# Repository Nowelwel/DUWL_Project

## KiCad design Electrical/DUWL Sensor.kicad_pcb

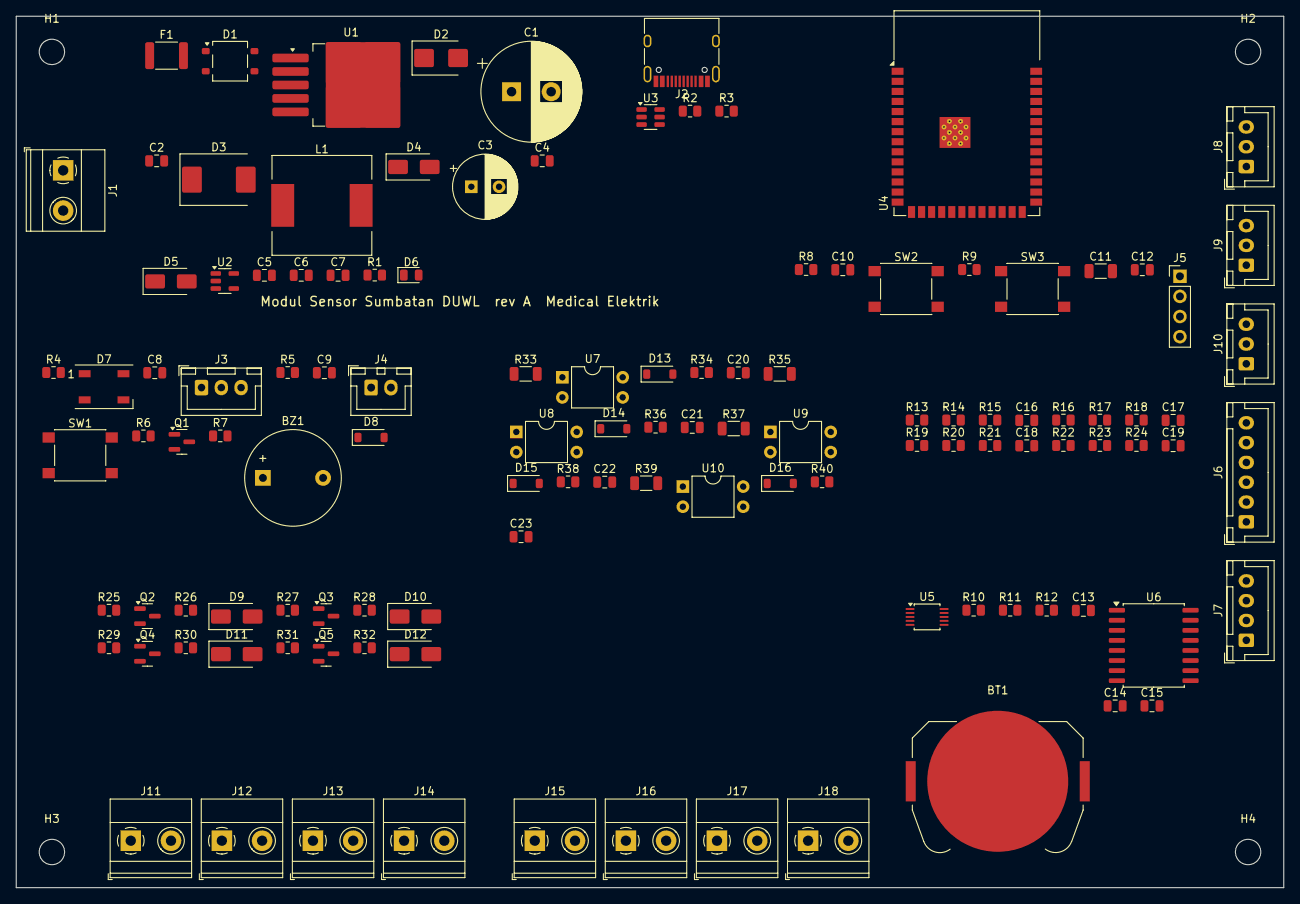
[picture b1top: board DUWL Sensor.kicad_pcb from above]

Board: 2 copper layers, 160.0 x 110.0 mm, 123 parts (0 on the bottom side), 69 nets, no tracks yet.

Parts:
BT1: CR2032; BatteryHolder_Keystone_3034_1x20mm
BZ1: Buzzer aktif 5V; Buzzer_12x9.5RM7.6
C1: 470u 63V; CP_Radial_D12.5mm_P5.00mm
C2: 100n 100V; C_0805_2012Metric
C3: 330u 16V; CP_Radial_D8.0mm_P3.50mm
C4, C7, C8, C9, C12, C13, C14, C15, C16, C17, C18, C19: 100nF; C_0805_2012Metric
C5, C6: 10uF; C_0805_2012Metric
C10, C20, C21, C22, C23: 1uF; C_0805_2012Metric
C11: 22uF; C_1206_3216Metric
D1: MB6S; TO-269AA
D2: SMBJ40CA; D_SMB
D3: SS36; D_SMC
D4, D5: SS14; D_SMA
D6: hijau; LED_0805_2012Metric
D7: WS2812B; LED_WS2812B_PLCC4_5.0x5.0mm_P3.2mm
D8, D13, D14, D15, D16: 1N4148W; D_SOD-123
D9, D10, D11, D12: SS16; D_SMA
F1: 0.5A 60V; Fuse_1812_4532Metric
H1, H2, H3, H4: M3; MountingHole_3.2mm_M3
J1: 24V IN AC/DC; TerminalBlock_Phoenix_MKDS-1,5-2-5.08_1x02_P5.08mm_Horizont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
J2: USB C 16P; USB_C_Receptacle_HRO_TYPE-C-31-M-12
J3: LED PANEL; JST_XH_B3B-XH-A_1x03_P2.50mm_Vertical
J4: TOMBOL EXT; JST_XH_B2B-XH-A_1x02_P2.50mm_Vertical
J5: UART DEBUG; PinHeader_1x04_P2.54mm_Vertical
J6: SLF3S-4000B; JST_XH_B6B-XH-A_1x06_P2.50mm_Vertical
J7: I2C EXT; JST_XH_B4B-XH-A_1x04_P2.50mm_Vertical
J8: PT1 SUPLAI; JST_XH_B3B-XH-A_1x03_P2.50mm_Vertical
J9: PT2 MANIFOLD; JST_XH_B3B-XH-A_1x03_P2.50mm_Vertical
J10: PT3 FASE 2; JST_XH_B3B-XH-A_1x03_P2.50mm_Vertical
J11: KATUP V1; TerminalBlock_Phoenix_MKDS-1,5-2-5.08_1x02_P5.08mm_Horizont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
J12: KATUP V2; TerminalBlock_Phoenix_MKDS-1,5-2-5.08_1x02_P5.08mm_Horizont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
J13: KATUP V3; TerminalBlock_Phoenix_MKDS-1,5-2-5.08_1x02_P5.08mm_Horizont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
J14: KATUP V4; TerminalBlock_Phoenix_MKDS-1,5-2-5.08_1x02_P5.08mm_Horizont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
J15: SOLENOID 1; TerminalBlock_Phoenix_MKDS-1,5-2-5.08_1x02_P5.08mm_Horizont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
J16: SOLENOID 2; TerminalBlock_Phoenix_MKDS-1,5-2-5.08_1x02_P5.08mm_Horizont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
J17: SOLENOID 3; TerminalBlock_Phoenix_MKDS-1,5-2-5.08_1x02_P5.08mm_Horizont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
J18: SOLENOID 4; TerminalBlock_Phoenix_MKDS-1,5-2-5.08_1x02_P5.08mm_Horizont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
L1: 68uH 2A; L_12x12mm_H6mm
Q1: 2N7002; SOT-23
Q2, Q3, Q4, Q5: AO3422; SOT-23
R1, R14, R17, R20, R23: 1k; R_0805_2012Metric
R2, R3: 5.1k; R_0805_2012Metric
R4: 330R; R_0805_2012Metric
R5, R8, R9, R12, R13, R16, R19, R22, R34, R36, R38, R40: 10k; R_0805_2012Metric
R6, R25, R27, R29, R31: 100R; R_0805_2012Metric
R7, R26, R28, R30, R32: 100k; R_0805_2012Metric
R10, R11: 4.7k; R_0805_2012Metric
R15, R18, R21, R24: 20k; R_0805_2012Metric
R33, R35, R37, R39: 10k; R_1206_3216Metric
SW1: CEK MANUAL; SW_SPST_PTS645
SW2: RESET; SW_SPST_PTS645
SW3: BOOT; SW_SPST_PTS645
U1: LM2596HVS-5.0; TO-263-5_TabPin3
U2: AP2112K-3.3; SOT-23-5
U3: USBLC6-2SC6; SOT-23-6
U4: ESP32-S3-WROOM-1-N8; ESP32-S3-WROOM-1
U5: ADS1115IDGS; TSSOP-10_3x3mm_P0.5mm
U6: DS3231SN; SOIC-16W_7.5x10.3mm_P1.27mm
U7, U8, U9, U10: PC817; DIP-4_W7.62mm

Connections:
+3V3: C6.1, C7.1, C11.1, C12.1, C13.1, C14.1, C15.1, J5.1, J6.3, J7.1, R1.1, R5.1, R8.1, R9.1, R10.1, R11.1, R12.1, R34.1, R36.1, R38.1, R40.1, U2.5, U4.2, U5.8, U6.2
+5V: C3.1, C4.1, D4.2, J8.1, J9.1, J10.1, L1.2, R22.1, U1.4
/AC1: F1.1, J1.1
/AC1_F: D1.2, F1.2
/AC2: D1.1, J1.2
/ADC_ALRT: R12.2, U4.18, U5.2
/AIN0: C16.1, R14.2, U5.4
/AIN1: C17.1, R17.2, U5.5
/AIN2: C18.1, R20.2, U5.6
/AIN3: C19.1, R23.2, U5.7
/BTN: C9.1, J4.1, R5.2, SW1.1, U4.22
/BUZZ: R6.1, U4.23
/BUZZ_D: BZ1.2, D8.2, Q1.3
/CC1: J2.A5, R2.1
/CC2: J2.B5, R3.1
/EN: C10.1, R8.2, SW2.1, U4.3
/IO0: R9.2, SW3.1, U4.27
/LED_DIN: R4.1, U4.31
/LED_DOUT: D7.2, J3.2
/PT1_SIG: J8.3, R13.1
/PT2_SIG: J9.3, R16.1
/PT3_SIG: J10.3, R19.1
/RXD0: J5.3, U4.36
/SCL: J6.5, J7.4, R11.2, U4.17, U5.10, U6.16
/SDA: J6.2, J7.3, R10.2, U4.12, U5.9, U6.15
/SOL1_A: J15.1, R33.1
/SOL1_K: D13.2, J15.2, U7.2
/SOL1_ST: C20.1, R34.2, U4.8, U7.4
/SOL2_A: J16.1, R35.1
/SOL2_K: D14.2, J16.2, U8.2
/SOL2_ST: C21.1, R36.2, U4.9, U8.4
/SOL3_A: J17.1, R37.1
/SOL3_K: D15.2, J17.2, U9.2
/SOL3_ST: C22.1, R38.2, U4.10, U9.4
/SOL4_A: J18.1, R39.1
/SOL4_K: D16.2, J18.2, U10.2
/SOL4_ST: C23.1, R40.2, U4.11, U10.4
/TXD0: J5.2, U4.37
/USB_DN: J2.A7, J2.B7, U3.3, U3.4, U4.13
/USB_DP: J2.A6, J2.B6, U3.1, U3.6, U4.14
/V1_OUT: D9.2, J11.2, Q2.3
/V2_OUT: D10.2, J12.2, Q3.3
/V3_OUT: D11.2, J13.2, Q4.3
/V4_OUT: D12.2, J14.2, Q5.3
/VBAT: BT1.1, U6.14
/VBUS: D5.2, J2.A4, J2.A9, J2.B4, J2.B9, U3.5
/VIN: C1.1, C2.1, D1.3, D2.2, D9.1, D10.1, D11.1, D12.1, J11.1, J12.1, J13.1, J14.1, U1.1
/VLV1: R25.1, U4.4
/VLV2: R27.1, U4.5
/VLV3: R29.1, U4.6
/VLV4: R31.1, U4.7
/VSYS: BZ1.1, C5.1, C8.1, D4.1, D5.1, D7.1, D8.1, J3.1, U2.1, U2.3
GND: BT1.2, C1.2, C2.2, C3.2, C4.2, C5.2, C6.2, C7.2, C8.2, C9.2, C10.2, C11.2, C12.2, C13.2, C14.2, C15.2, C16.2, C17.2, C18.2, C19.2, C20.2, C21.2, C22.2, C23.2, D1.4, D2.1, D3.2, D6.1, D7.3, J2.A1, J2.A12, J2.B1, J2.B12, J2.S1, J3.3, J4.2, J5.4, J6.4, J7.2, J8.2, J9.2, J10.2, Q1.2, Q2.2, Q3.2, Q4.2, Q5.2, R2.2, R3.2, R7.2, R15.2, R18.2, R21.2, R24.2, R26.2, R28.2, R30.2, R32.2, SW1.2, SW2.2, SW3.2, U1.3, U1.5, U2.2, U3.2, U4.1, U4.40, U4.41, U5.1, U5.3, U6.5, U6.6, U6.7, U6.8, U6.9, U6.10, U6.11, U6.12, U6.13, U7.3, U8.3, U9.3, U10.3
unnamed: D3.1, L1.1, U1.2
unnamed: D6.2, R1.2
unnamed: D7.4, R4.2
unnamed: D13.1, R33.2, U7.1
unnamed: D14.1, R35.2, U8.1
unnamed: D15.1, R37.2, U9.1
unnamed: D16.1, R39.2, U10.1
unnamed: Q1.1, R6.2, R7.1
unnamed: Q2.1, R25.2, R26.1
unnamed: Q3.1, R27.2, R28.1
unnamed: Q4.1, R29.2, R30.1
unnamed: Q5.1, R31.2, R32.1
unnamed: R13.2, R14.1, R15.1
unnamed: R16.2, R17.1, R18.1
unnamed: R19.2, R20.1, R21.1
unnamed: R22.2, R23.1, R24.1
